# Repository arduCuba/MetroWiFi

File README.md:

**Mainboard MetroWiFI(wip)**
[:parking:re release](https://github.com/arduCuba/MetroWiFi/releases/tag/Beta_4)

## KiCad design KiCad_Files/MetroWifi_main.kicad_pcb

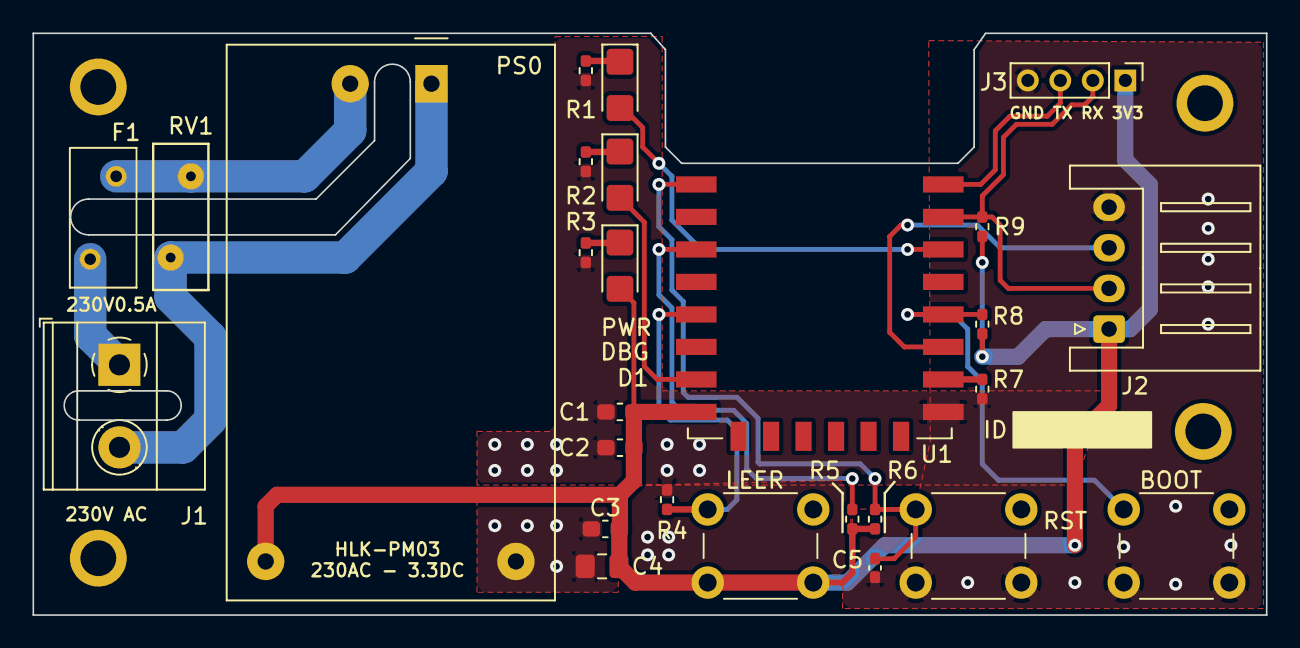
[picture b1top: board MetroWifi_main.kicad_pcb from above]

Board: 2 copper layers, 75.9 x 35.8 mm, 27 parts (0 on the bottom side), 18 nets.

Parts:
BOOT: SW_Push; SW_PUSH_6mm_H5mm
C1, C3: 0.1uF; C_0603_1608Metric_Pad1.08x0.95mm_HandSolder
C2: 10uF; C_0603_1608Metric_Pad1.08x0.95mm_HandSolder
C4: 470uF; C_0805_2012Metric_Pad1.18x1.45mm_HandSolder
C5: 10k; C_0402_1005Metric_Pad0.74x0.62mm_HandSolder
D1: LED; LED_1206_3216Metric_Castellated
DBG: LED; LED_1206_3216Metric_Castellated
F1: 220/0.5A; Fuse_BelFuse_0ZRE0005FF_L8.3mm_W3.8mm
J1: 230; TerminalBlock_Phoenix_MKDS-1,5-2-5.08_1x02_P5.08mm_Horizont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
J2: CNX_IR; JST_XH_S4B-XH-A_1x04_P2.50mm_Horizontal
J3: Programar; PinHeader_1x04_P2.00mm_Vertical
LEER: SW_Push; SW_PUSH_6mm_H5mm
PS0: HLK-PM03; Converter_ACDC_HiLink_HLK-PMxx
PWR: LED; LED_1206_3216Metric_Castellated
R1, R2, R3: 220; R_0402_1005Metric_Pad0.72x0.64mm_HandSolder
R4, R5, R6, R7, R8, R9: 10k; R_0402_1005Metric_Pad0.72x0.64mm_HandSolder
RST: SW_Push; SW_PUSH_6mm_H5mm
RV1: V230LA4; RV_Disc_D9mm_W3.4mm_P5mm
U1: ESP-12F; ESP-12E

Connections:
BT: BOOT.2, R8.2, U1.18
GNDD: BOOT.1, C1.2, C2.2, C3.2, C4.2, C5.2, J2.4, J3.4, PS0.3, R1.1, R2.1, R3.2, R4.1, R7.1, RST.1, U1.15
unnamed: D1.1, R3.1
unnamed: PWR.1, R1.2
unnamed: DBG.1, R2.2
unnamed: F1.1, PS0.2, RV1.1
unnamed: F1.2, J1.1
unnamed: J1.2, PS0.1, RV1.2
unnamed: J2.2, J3.2, R9.1, U1.21
unnamed: J3.3, U1.22
unnamed: R5.1, U1.3
unnamed: R7.2, U1.16
P5: PWR.2, U1.20
P13: DBG.2, U1.7
PR: LEER.2, R4.2, U1.5
RS: C5.1, R6.1, RST.2, U1.1
TX: J2.3, U1.17
VCC: C1.1, C2.1, C3.1, C4.1, D1.2, J2.1, J3.1, LEER.1, PS0.4, R5.2, R6.2, R8.1, R9.2, U1.8

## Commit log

2021-05-15 Mainboard
